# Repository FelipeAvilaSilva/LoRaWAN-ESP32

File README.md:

# LoRaWAN-ESP32
  This code is responsible for real-time data communication and will be implemented in the autonomous kayak using LoRaWAN protocol at frequencies of 915 MHz.

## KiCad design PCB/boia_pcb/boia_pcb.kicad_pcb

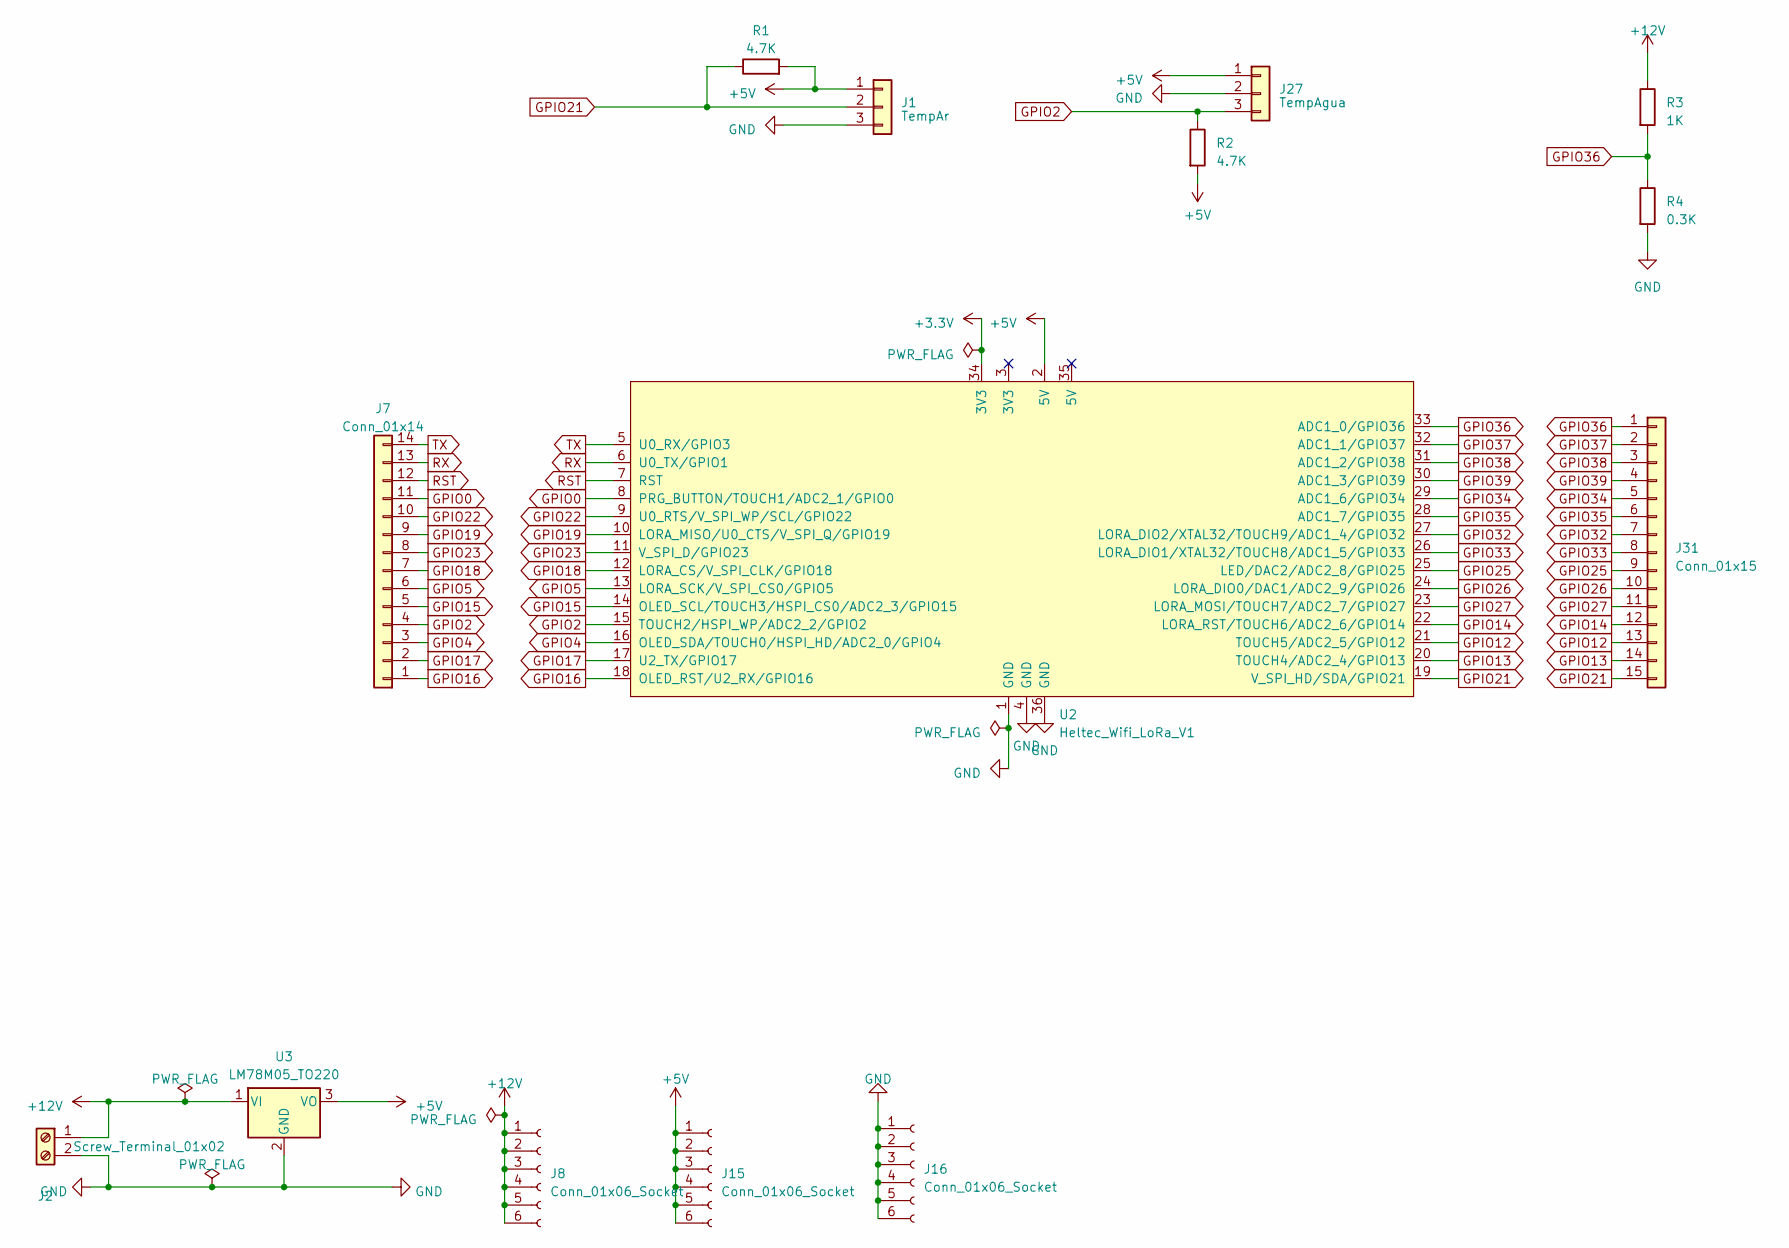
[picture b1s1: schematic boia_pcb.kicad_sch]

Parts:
J1: TempAr; PinSocket_1x03_P2.54mm_Vertical
J2: Screw_Terminal_01x02; TerminalBlock_Phoenix_MKDS-1,5-2-5.08_1x02_P5.08mm_Horizont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
J7: Conn_01x14; PinSocket_1x14_P2.54mm_Vertical
J8, J15, J16: Conn_01x06_Socket; PinSocket_1x06_P2.54mm_Vertical
J27: TempAgua; PinSocket_1x03_P2.54mm_Vertical
J31: Conn_01x15; PinSocket_1x15_P2.54mm_Vertical
R1, R2: 4.7K; R_Axial_DIN0207_L6.3mm_D2.5mm_P7.62mm_Horizontal
R3: 1K; R_Axial_DIN0207_L6.3mm_D2.5mm_P7.62mm_Horizontal
R4: 0.3K; R_Axial_DIN0207_L6.3mm_D2.5mm_P7.62mm_Horizontal
U2: Heltec_Wifi_LoRa_V1; Heltec_WiFi_LoRa_V2
U3: LM78M05_TO220; TO255P1020X450X2000-3

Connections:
+3.3V: U2.34 (3V3)
+5V: J1.1, J15.1, J15.2, J15.3, J15.4, J15.5, J15.6, J27.1, R1.2, R2.2, U2.2 (5V), U3.3 (VO)
+12V: J2.1, J8.1, J8.2, J8.3, J8.4, J8.5, J8.6, R3.1, U3.1 (VI)
GND: J1.3, J2.2, J16.1, J16.2, J16.3, J16.4, J16.5, J16.6, J27.2, R4.2, U2.1 (GND), U2.4 (GND), U2.36 (GND), U3.2 (GND)
GPIO0: J7.11, U2.8 (PRG_BUTTON/TOUCH1/ADC2_1/GPIO0)
GPIO2: J7.4, J27.3, R2.1, U2.15 (TOUCH2/HSPI_WP/ADC2_2/GPIO2)
GPIO4: J7.3, U2.16 (OLED_SDA/TOUCH0/HSPI_HD/ADC2_0/GPIO4)
GPIO5: J7.6, U2.13 (LORA_SCK/V_SPI_CS0/GPIO5)
GPIO12: J31.13, U2.21 (TOUCH5/ADC2_5/GPIO12)
GPIO13: J31.14, U2.20 (TOUCH4/ADC2_4/GPIO13)
GPIO14: J31.12, U2.22 (LORA_RST/TOUCH6/ADC2_6/GPIO14)
GPIO15: J7.5, U2.14 (OLED_SCL/TOUCH3/HSPI_CS0/ADC2_3/GPIO15)
GPIO16: J7.1, U2.18 (OLED_RST/U2_RX/GPIO16)
GPIO17: J7.2, U2.17 (U2_TX/GPIO17)
GPIO18: J7.7, U2.12 (LORA_CS/V_SPI_CLK/GPIO18)
GPIO19: J7.9, U2.10 (LORA_MISO/U0_CTS/V_SPI_Q/GPIO19)
GPIO21: J1.2, J31.15, R1.1, U2.19 (V_SPI_HD/SDA/GPIO21)
GPIO22: J7.10, U2.9 (U0_RTS/V_SPI_WP/SCL/GPIO22)
GPIO23: J7.8, U2.11 (V_SPI_D/GPIO23)
GPIO25: J31.9, U2.25 (LED/DAC2/ADC2_8/GPIO25)
GPIO26: J31.10, U2.24 (LORA_DIO0/DAC1/ADC2_9/GPIO26)
GPIO27: J31.11, U2.23 (LORA_MOSI/TOUCH7/ADC2_7/GPIO27)
GPIO32: J31.7, U2.27 (LORA_DIO2/XTAL32/TOUCH9/ADC1_4/GPIO32)
GPIO33: J31.8, U2.26 (LORA_DIO1/XTAL32/TOUCH8/ADC1_5/GPIO33)
GPIO34: J31.5, U2.29 (ADC1_6/GPIO34)
GPIO35: J31.6, U2.28 (ADC1_7/GPIO35)
GPIO36: J31.1, R3.2, R4.1, U2.33 (ADC1_0/GPIO36)
GPIO37: J31.2, U2.32 (ADC1_1/GPIO37)
GPIO38: J31.3, U2.31 (ADC1_2/GPIO38)
GPIO39: J31.4, U2.30 (ADC1_3/GPIO39)
RST: J7.12, U2.7 (RST)
RX: J7.13, U2.6 (U0_TX/GPIO1)
TX: J7.14, U2.5 (U0_RX/GPIO3)

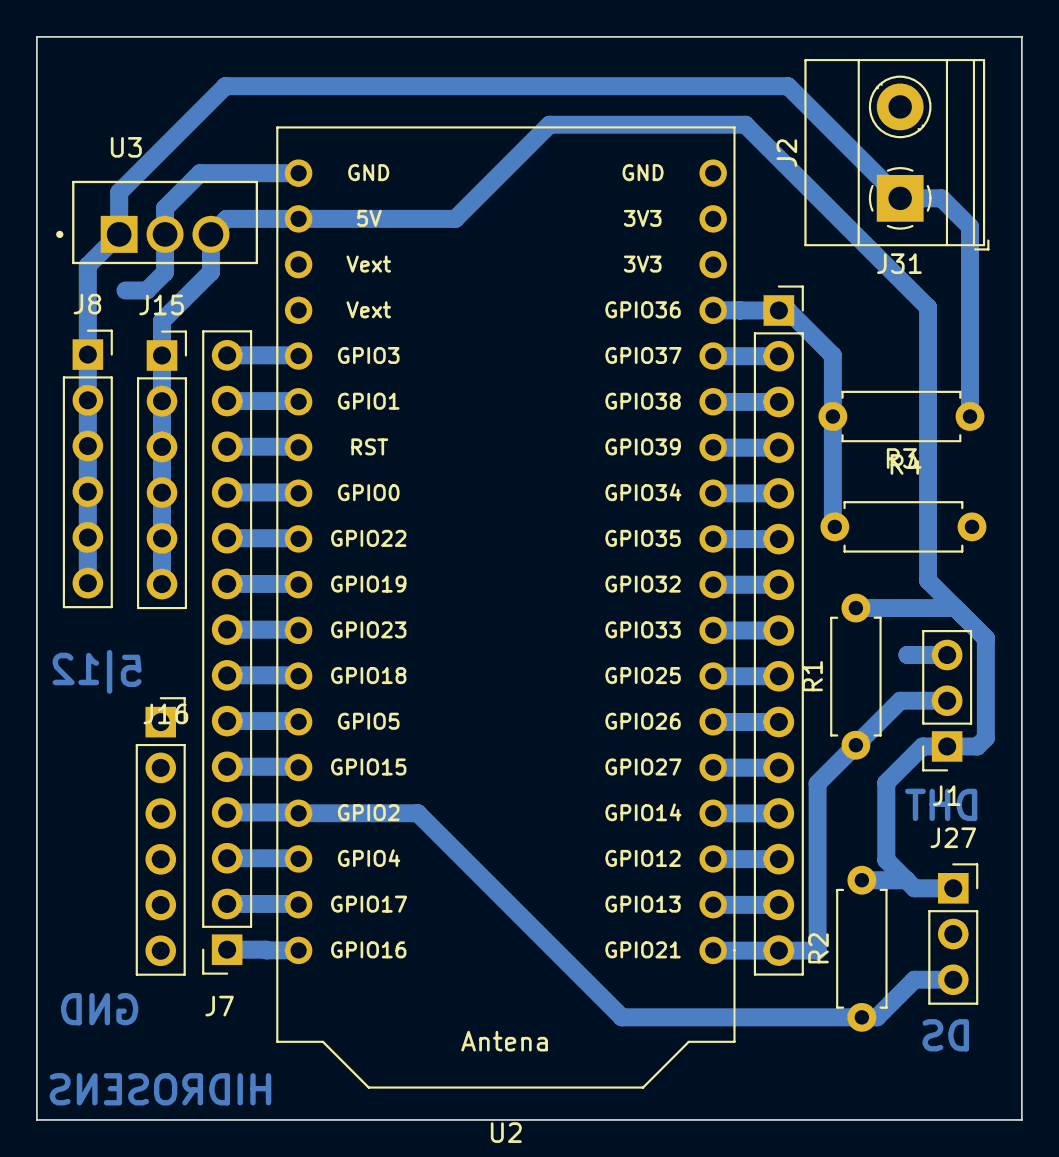
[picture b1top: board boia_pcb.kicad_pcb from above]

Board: 2 copper layers, 54.7 x 60.2 mm, 14 parts (0 on the bottom side), 32 nets.

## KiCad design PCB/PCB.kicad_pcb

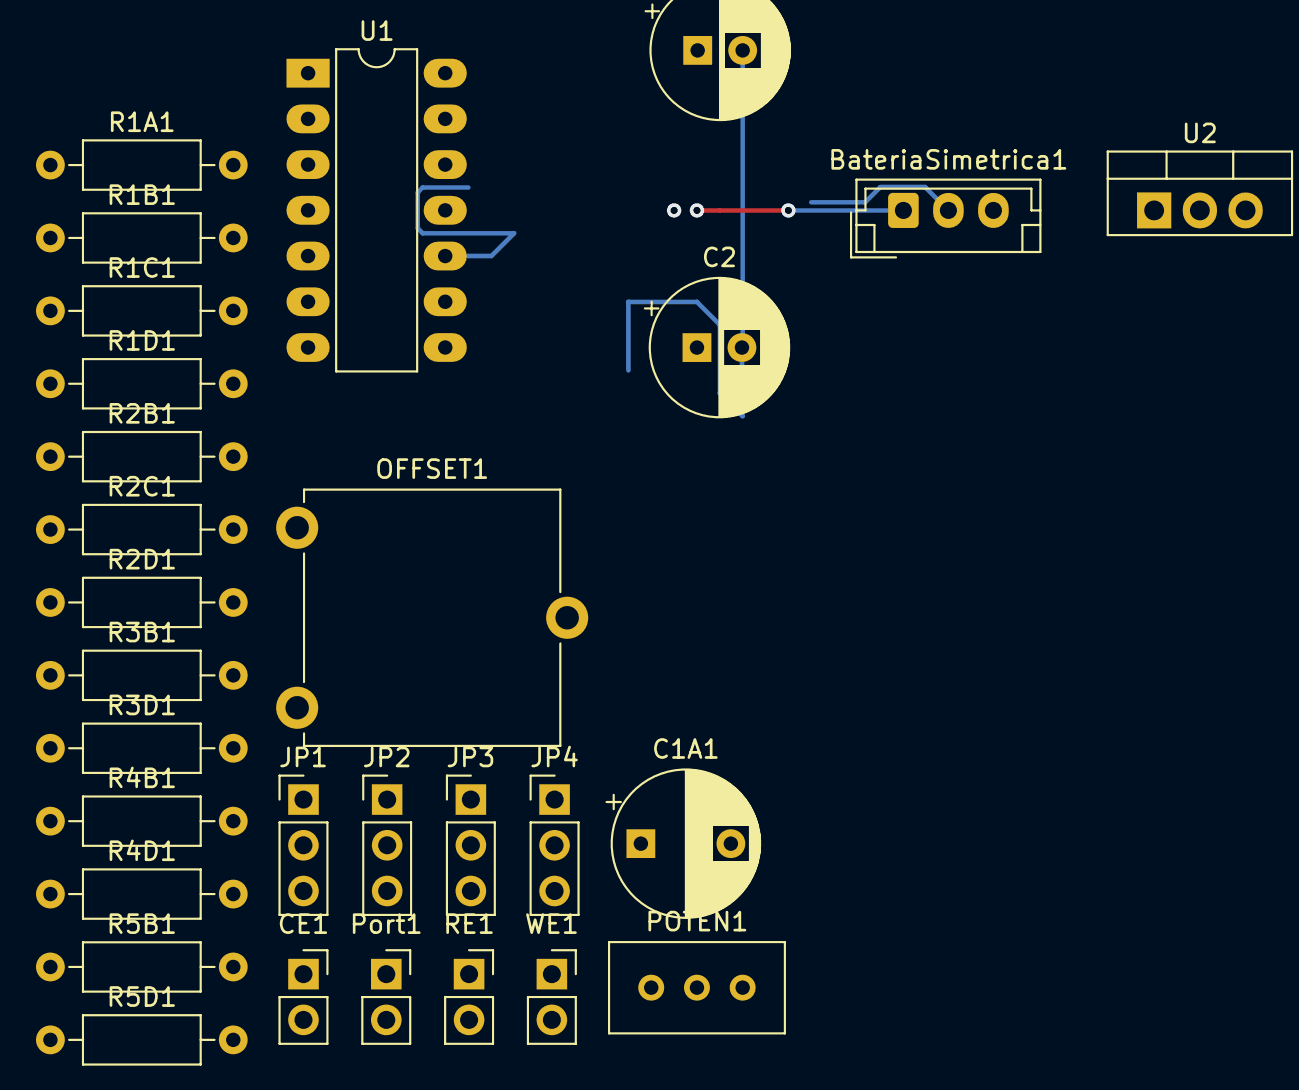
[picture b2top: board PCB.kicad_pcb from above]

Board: 2 copper layers, 29 parts (0 on the bottom side), 25 nets.

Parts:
BateriaSimetrica1: Screw_Terminal_01x03; JST_EH_B3B-EH-A_1x03_P2.50mm_Vertical
C1, C2: 3.3uF; CP_Radial_D7.5mm_P2.50mm
C1A1: C_Polarized; CP_Radial_D8.0mm_P5.00mm
CE1: Screw_Terminal_01x01; PinSocket_1x02_P2.54mm_Vertical
JP1, JP2, JP3, JP4: Jumper_3_Bridged12; PinHeader_1x03_P2.54mm_Vertical
OFFSET1: R_Potentiometer_Trim; Potentiometer_ACP_CA14V-15_Vertical
POTEN1: LM741; Potentiometer_Bourns_3296W_Vertical
Port1: PortA0; PinSocket_1x02_P2.54mm_Vertical
R1A1: 10k; R_Axial_DIN0207_L6.3mm_D2.5mm_P10.16mm_Horizontal
R1B1, R1D1, R2D1, R4D1: 1k; R_Axial_DIN0207_L6.3mm_D2.5mm_P10.16mm_Horizontal
R1C1: 2.2K; R_Axial_DIN0207_L6.3mm_D2.5mm_P10.16mm_Horizontal
R2B1, R3D1: 160; R_Axial_DIN0207_L6.3mm_D2.5mm_P10.16mm_Horizontal
R2C1: 2.2k; R_Axial_DIN0207_L6.3mm_D2.5mm_P10.16mm_Horizontal
R3B1, R4B1: 1K; R_Axial_DIN0207_L6.3mm_D2.5mm_P10.16mm_Horizontal
R5B1: 300; R_Axial_DIN0207_L6.3mm_D2.5mm_P10.16mm_Horizontal
R5D1: 3.3k; R_Axial_DIN0207_L6.3mm_D2.5mm_P10.16mm_Horizontal
RE1: Screw_Terminal_01x01; PinSocket_1x02_P2.54mm_Vertical
U1: LM324; DIP-14_W7.62mm_LongPads
U2: L7805; TO-220-3_Vertical
WE1: Screw_Terminal_01x01; PinSocket_1x02_P2.54mm_Vertical

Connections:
+5V: C2.1, R4B1.1, R5D1.2, U2.3 (OUT)
+12V: BateriaSimetrica1.1, C1.1, U1.4 (V+), U2.1 (IN)
-12V: BateriaSimetrica1.3, OFFSET1.2, U1.11 (V-)
GND: BateriaSimetrica1.2, C1.2, C1A1.2, C2.2, R2D1.1, R3B1.1, U1.10 (+), U2.2 (GND)
unnamed: CE1.1, JP3.3 (B)
unnamed: JP1.1 (A), JP3.1 (A), JP4.2 (C)
unnamed: JP1.3 (B), WE1.1
unnamed: JP1.2 (C), JP2.3 (B), POTEN1.2 (-)
unnamed: JP2.1 (A), R5B1.1, U1.7
unnamed: JP2.2 (C), POTEN1.3 (+)
unnamed: JP4.1 (A), R1C1.1
unnamed: JP4.3 (B), RE1.1
unnamed: OFFSET1.1, POTEN1.1 (NULL)
unnamed: Port1.1, R1A1.1
unnamed: Port1.2, R4D1.2, U1.14
unnamed: R1B1.2, R2B1.1
unnamed: R1D1.1, R2C1.2, U1.8
unnamed: R3D1.1, R4D1.1
unnamed: C1A1.1, R1A1.2, U1.3 (+)
unnamed: R1B1.1, U1.1, U1.2 (-)
unnamed: R2B1.2, R3B1.2, U1.5 (+)
unnamed: R4B1.2, R5B1.2, U1.6 (-)
unnamed: R1C1.2, R2C1.1, U1.9 (-)
unnamed: R1D1.2, R5D1.1, U1.12 (+)
unnamed: R2D1.2, R3D1.2, U1.13 (-)

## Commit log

2022-07-25 git ignore
2022-07-26 include battery voltage
2022-07-28 add lib LoRaWan
2022-07-28 add lib sd and dht
2022-07-29 add flags
2022-07-29 fix readSensor
2022-08-04 add gps module
2022-08-07 init fix gps module
    fix parcial
2022-08-07 fix bugs
2022-08-07 add payload
2022-08-09 fix millis
2022-08-11 fix gps
2022-11-01 add temp agua
2023-04-24 add pbc kicad
2023-04-25 add pcb
2023-04-25 att esquematico
    rotulos, ligações
2023-05-05 add footprint
2023-06-21 Add boia
    sensor de temp agua ok
2023-10-04 att 30 min
    send message
2023-12-14 add lib
